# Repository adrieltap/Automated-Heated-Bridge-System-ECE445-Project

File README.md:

# ACADEMIC INTEGRITY
Please review the University of Illinois Student Code before starting, particularly all subsections of Article 1, Part 4 Academic Integrity and Procedure here.

§ 1‑402 Academic Integrity Infractions

(a). Cheating. No student shall use or attempt to use in any academic exercise materials, information, study aids, or electronic data that the student knows or should know is unauthorized. Instructors are strongly encouraged to make in advance a clear statement of their policies and procedures concerning the use of shared study aids, examination files, and related materials and forms of assistance. Such advance notification is especially important in the case of take-home examinations. During any examination, students should assume that external assistance (e.g., books, notes, calculators, and communications with others) is prohibited unless specifically authorized by the Instructor. A violation of this section includes but is not limited to:

(1) Allowing others to conduct research or prepare any work for a student without prior authorization from the Instructor, including using the services of commercial term paper companies.

(2) Submitting substantial portions of the same academic work for credit more than once or by more than one student without authorization from the Instructors to whom the work is being submitted.

(3) Working with another person without authorization to satisfy an individual assignment.

(b) Plagiarism. No student shall represent the words, work, or ideas of another as his or her own in any academic endeavor. A violation of this section includes but is not limited to:

(1) Copying: Submitting the work of another as one’s own.

(2) Direct Quotation: Every direct quotation must be identified by quotation marks or by appropriate indentation and must be promptly cited. Proper citation style for many academic departments is outlined in such manuals as the MLA Handbook or K.L. Turabian’s A Manual for Writers of Term Papers, Theses and Dissertations. These and similar publications are available in the University bookstore or library. The actual source from which cited information was obtained should be acknowledged.

(3) Paraphrase: Prompt acknowledgment is required when material from another source is paraphrased or summarized in whole or in part. This is true even if the student’s words differ substantially from those of the source. A citation acknowledging only a directly quoted statement does not suffice as an acknowledgment of any preceding or succeeding paraphrased material.

(4) Borrowed Facts or Information: Information obtained in one’s reading or research that is not common knowledge must be acknowledged. Examples of common knowledge might include the names of leaders of prominent nations, basic scientific laws, etc. Materials that contribute only to one’s general understanding of the subject may be acknowledged in a bibliography and need not be immediately cited. One citation is usually sufficient to acknowledge indebtedness when a number of connected sentences in the paper draw their special information from one source.

(c) Fabrication. No student shall falsify or invent any information or citation in an academic endeavor. A violation of this section includes but is not limited to:

(1) Using invented information in any laboratory experiment or other academic endeavor without notice to and authorization from the Instructor or examiner. It would be improper, for example, to analyze one sample in an experiment and covertly invent data based on that single experiment for several more required analyses.

(2) Altering the answers given for an exam after the examination has been graded.

(3) Providing false or misleading information for the purpose of gaining an academic advantage.

(d) Facilitating Infractions of Academic Integrity. No student shall help or attempt to help another to commit an infraction of academic integrity, where one knows or should know that through one’s acts or omissions such an infraction may be facilitated. A violation of this section includes but is not limited to:

(1) Allowing another to copy from one’s work.

(2) Taking an exam by proxy for someone else. This is an infraction of academic integrity on the part of both the student enrolled in the course and the proxy or substitute.

(3) Removing an examination or quiz from a classroom, faculty office, or other facility without authorization.

(e) Bribes, Favors, and Threats. No student shall bribe or attempt to bribe, promise favors to or make threats against any person with the intent to affect a record of a grade or evaluation of academic performance. This includes conspiracy with another person who then takes the action on behalf of the student.

(f) Academic Interference. No student shall tamper with, alter, circumvent, or destroy any educational material or resource in a manner that deprives any other student of fair access or reasonable use of that material or resource.

(1) Educational resources include but are not limited to computer facilities, electronic data, required/reserved readings, reference works, or other library materials.

(2) Academic interference also includes acts in which the student committing the infraction personally benefits from the interference, regardless of the effect on other students.

LEGAL
Permission to use, copy, modify, and distribute this software and its documentation for any purpose, without fee, and without written agreement is hereby granted, provided that the above copyright notice and the following two paragraphs appear in all copies of this software.

IN NO EVENT SHALL THE AUTHOR OR THE UNIVERSITY OF ILLINOIS BE LIABLE TO ANY PARTY FOR DIRECT, INDIRECT, SPECIAL, INCIDENTAL, OR CONSEQUENTIAL DAMAGES ARISING OUT OF THE USE OF THIS SOFTWARE AND ITS DOCUMENTATION, EVEN IF THE AUTHOR AND/OR THE UNIVERSITY OF ILLINOIS HAS BEEN ADVISED OF THE POSSIBILITY OF SUCH DAMAGE.

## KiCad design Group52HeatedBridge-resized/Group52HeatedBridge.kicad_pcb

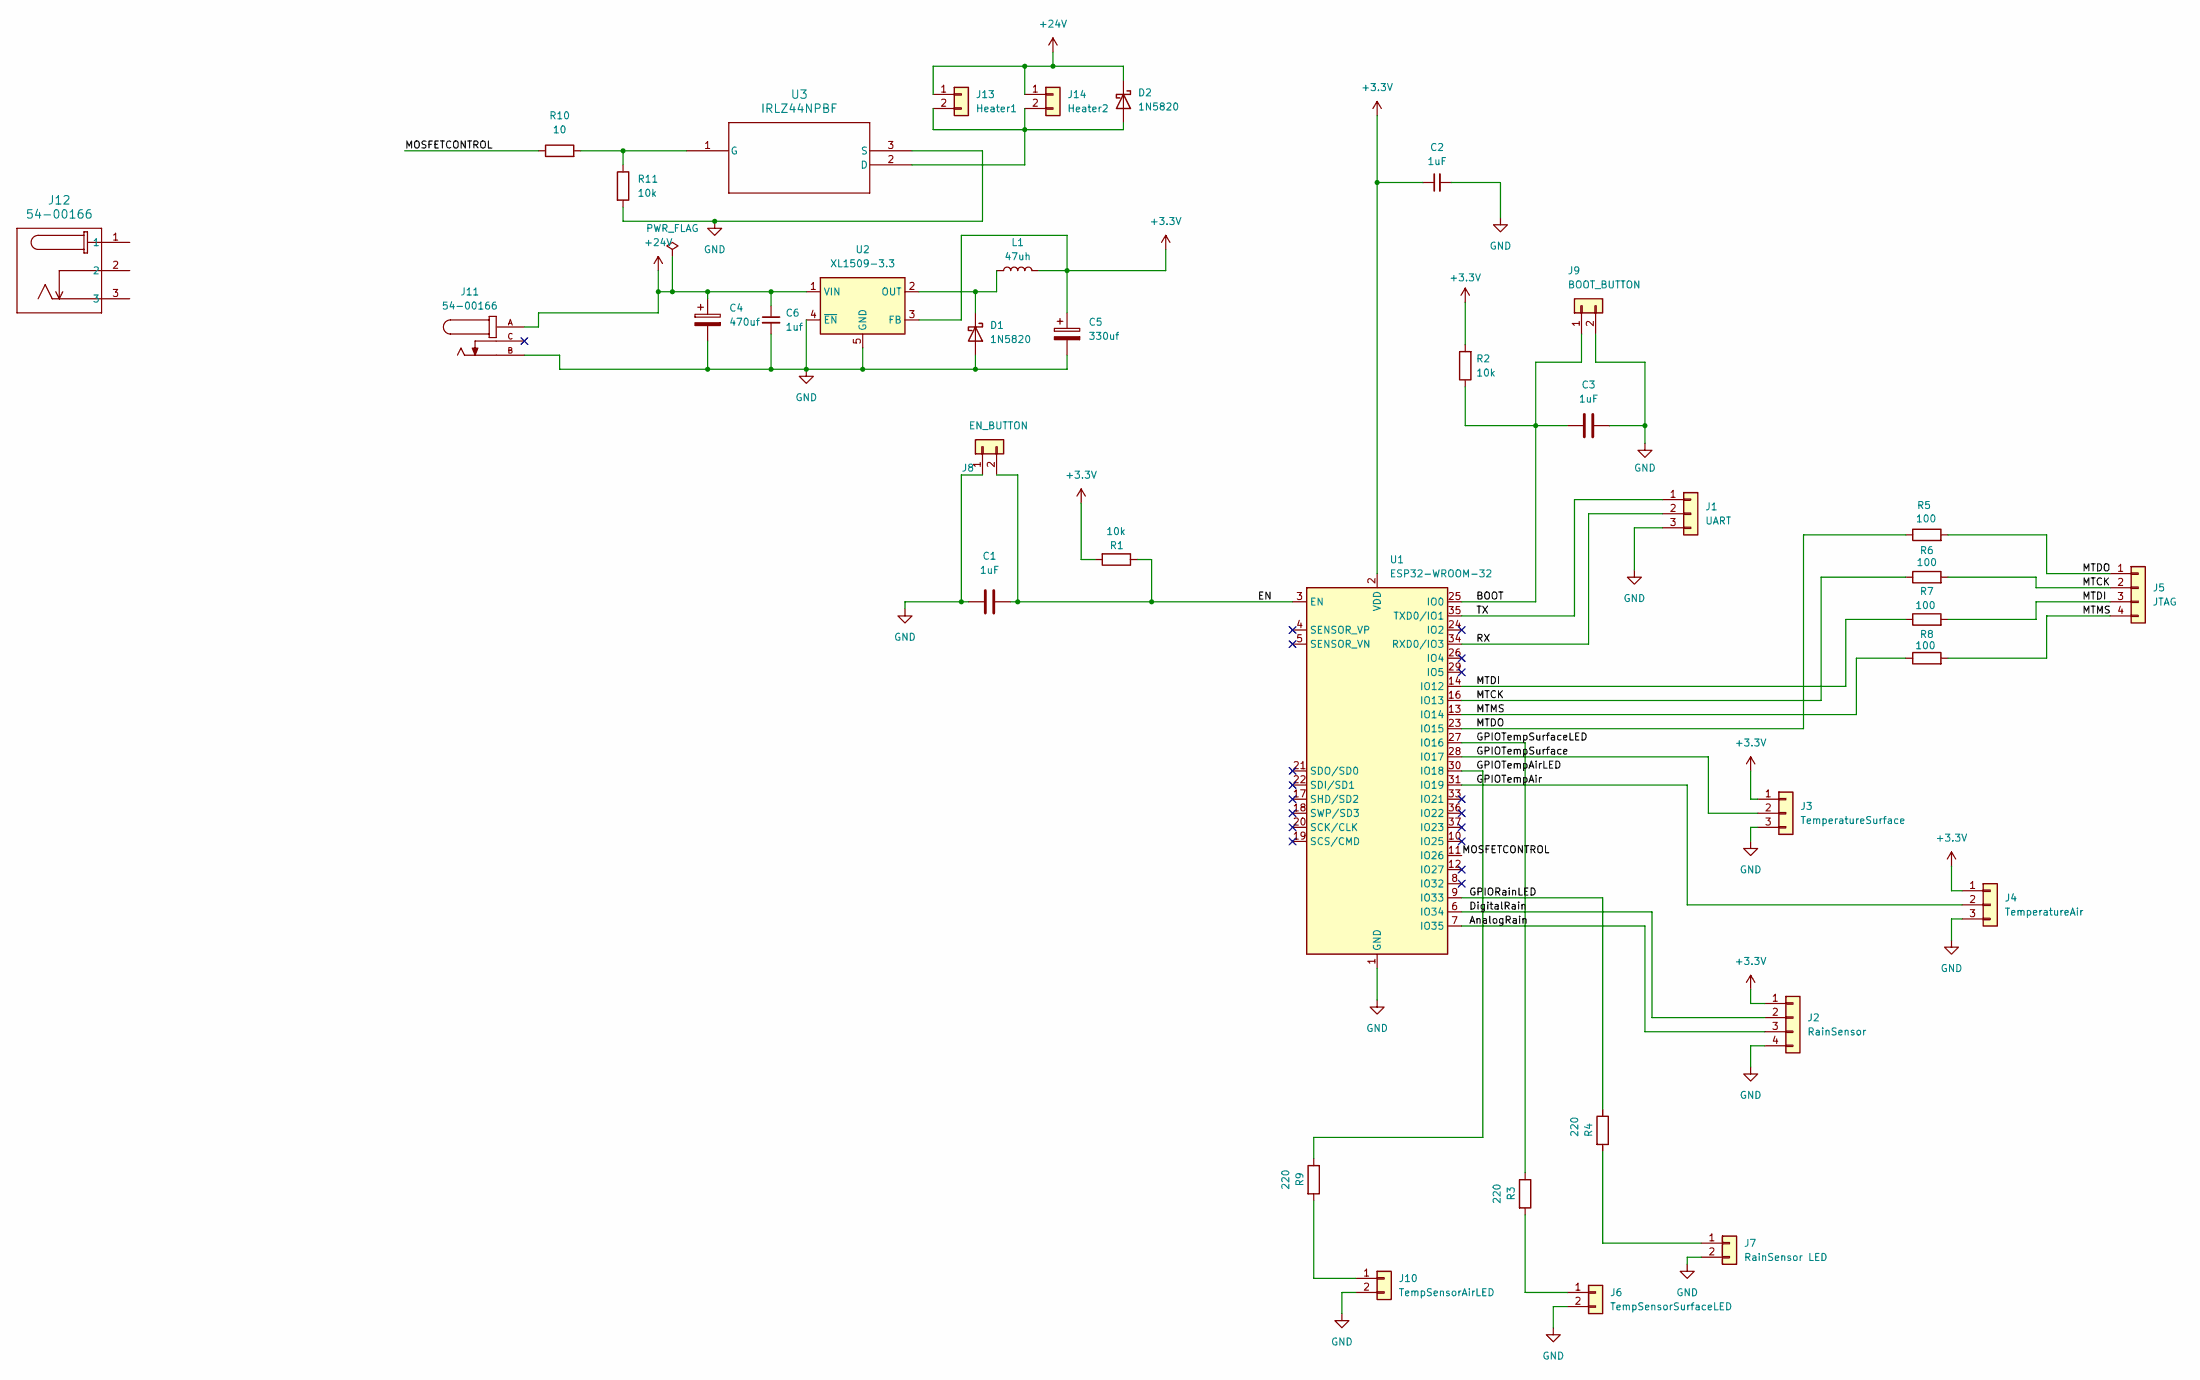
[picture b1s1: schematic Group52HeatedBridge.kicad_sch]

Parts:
C1, C2, C3: 1uF; C_0805_2012Metric_Pad1.18x1.45mm_HandSolder
C4: 470uf; C_0805_2012Metric_Pad1.18x1.45mm_HandSolder
C5: 330uf; C_0805_2012Metric_Pad1.18x1.45mm_HandSolder
C6: 1uf; C_0805_2012Metric_Pad1.18x1.45mm_HandSolder
D1, D2: 1N5820; D_DO-201AD_P3.81mm_Vertical_KathodeUp
J1: UART; Molex_KK-254_AE-6410-03A_1x03_P2.54mm_Vertical
J2: RainSensor; Molex_KK-254_AE-6410-04A_1x04_P2.54mm_Vertical
J3: TemperatureSurface; Molex_KK-254_AE-6410-03A_1x03_P2.54mm_Vertical
J4: TemperatureAir; Molex_KK-254_AE-6410-03A_1x03_P2.54mm_Vertical
J5: JTAG; Molex_KK-254_AE-6410-04A_1x04_P2.54mm_Vertical
J6: TempSensorSurfaceLED; Molex_KK-254_AE-6410-02A_1x02_P2.54mm_Vertical
J7: RainSensor LED; Molex_KK-254_AE-6410-02A_1x02_P2.54mm_Vertical
J8: EN_BUTTON; Molex_KK-254_AE-6410-02A_1x02_P2.54mm_Vertical
J9: BOOT_BUTTON; Molex_KK-254_AE-6410-02A_1x02_P2.54mm_Vertical
J10: TempSensorAirLED; Molex_KK-254_AE-6410-02A_1x02_P2.54mm_Vertical
J11: 54-00166; TENSILITY_54-00166; PARTREV A
J12: 54-00166; TENSILITY_54-00166
J13: Heater1; Molex_KK-254_AE-6410-02A_1x02_P2.54mm_Vertical
J14: Heater2; Molex_KK-254_AE-6410-02A_1x02_P2.54mm_Vertical
L1: 47uh; L_0805_2012Metric_Pad1.15x1.40mm_HandSolder
R1, R2, R11: 10k; R_0805_2012Metric_Pad1.20x1.40mm_HandSolder
R3, R4, R9: 220; R_0805_2012Metric_Pad1.20x1.40mm_HandSolder
R5, R6, R7, R8: 100; R_0805_2012Metric_Pad1.20x1.40mm_HandSolder
R10: 10; R_0805_2012Metric_Pad1.20x1.40mm_HandSolder
U1: ESP32-WROOM-32
U2: XL1509-3.3; SOIC-8_3.9x4.9mm_P1.27mm
U3: IRLZ44NPBF; PG-TO220-3_INF

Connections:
+3.3V: C2.1, C5.1, J2.1, J3.1, J4.1, L1.2, R1.2, R2.2, U1.2 (VDD), U2.3 (FB)
+24V: C4.1, C6.1, D2.1 (K), J11.A, J13.1, J14.1, U2.1 (VIN)
/AnalogRain: J2.3, U1.7 (IO35)
/BOOT: C3.1, J9.1, R2.1, U1.25 (IO0)
/DigitalRain: J2.2, U1.6 (IO34)
/EN: C1.2, J8.2, R1.1, U1.3 (EN)
/GPIORainLED: R4.1, U1.9 (IO33)
/GPIOTempAir: J4.2, U1.31 (IO19)
/GPIOTempAirLED: R9.1, U1.30 (IO18)
/GPIOTempSurface: J3.2, U1.28 (IO17)
/GPIOTempSurfaceLED: R3.1, U1.27 (IO16)
/MOSFETCONTROL: R10.1, U1.11 (IO26)
/MTCK: J5.2, R6.1, R6.2, U1.16 (IO13)
/MTDI: J5.3, R7.1, R7.2, U1.14 (IO12)
/MTDO: J5.1, R5.1, R5.2, U1.23 (IO15)
/MTMS: J5.4, R8.1, R8.2, U1.13 (IO14)
/RX: J1.2, U1.34 (RXD0/IO3)
/TX: J1.1, U1.35 (TXD0/IO1)
GND: C1.1, C2.2, C3.2, C4.2, C5.2, C6.2, D1.2 (A), J1.3, J2.4, J3.3, J4.3, J6.2, J7.2, J8.1, J9.2, J10.2, J11.B, R11.2, U1.1 (GND), U1.15 (GND), U1.38 (GND), U1.39 (GND), U2.4 (~EN), U2.5 (GND), U2.6 (GND), U2.7 (GND), U2.8 (GND), U3.3 (S)
unnamed: D1.1 (K), L1.1, U2.2 (OUT)
unnamed: D2.2 (A), J13.2, J14.2, U3.2 (D)
unnamed: J6.1, R3.2
unnamed: J7.1, R4.2
unnamed: J10.1, R9.2
unnamed: R10.2, R11.1, U3.1 (G)

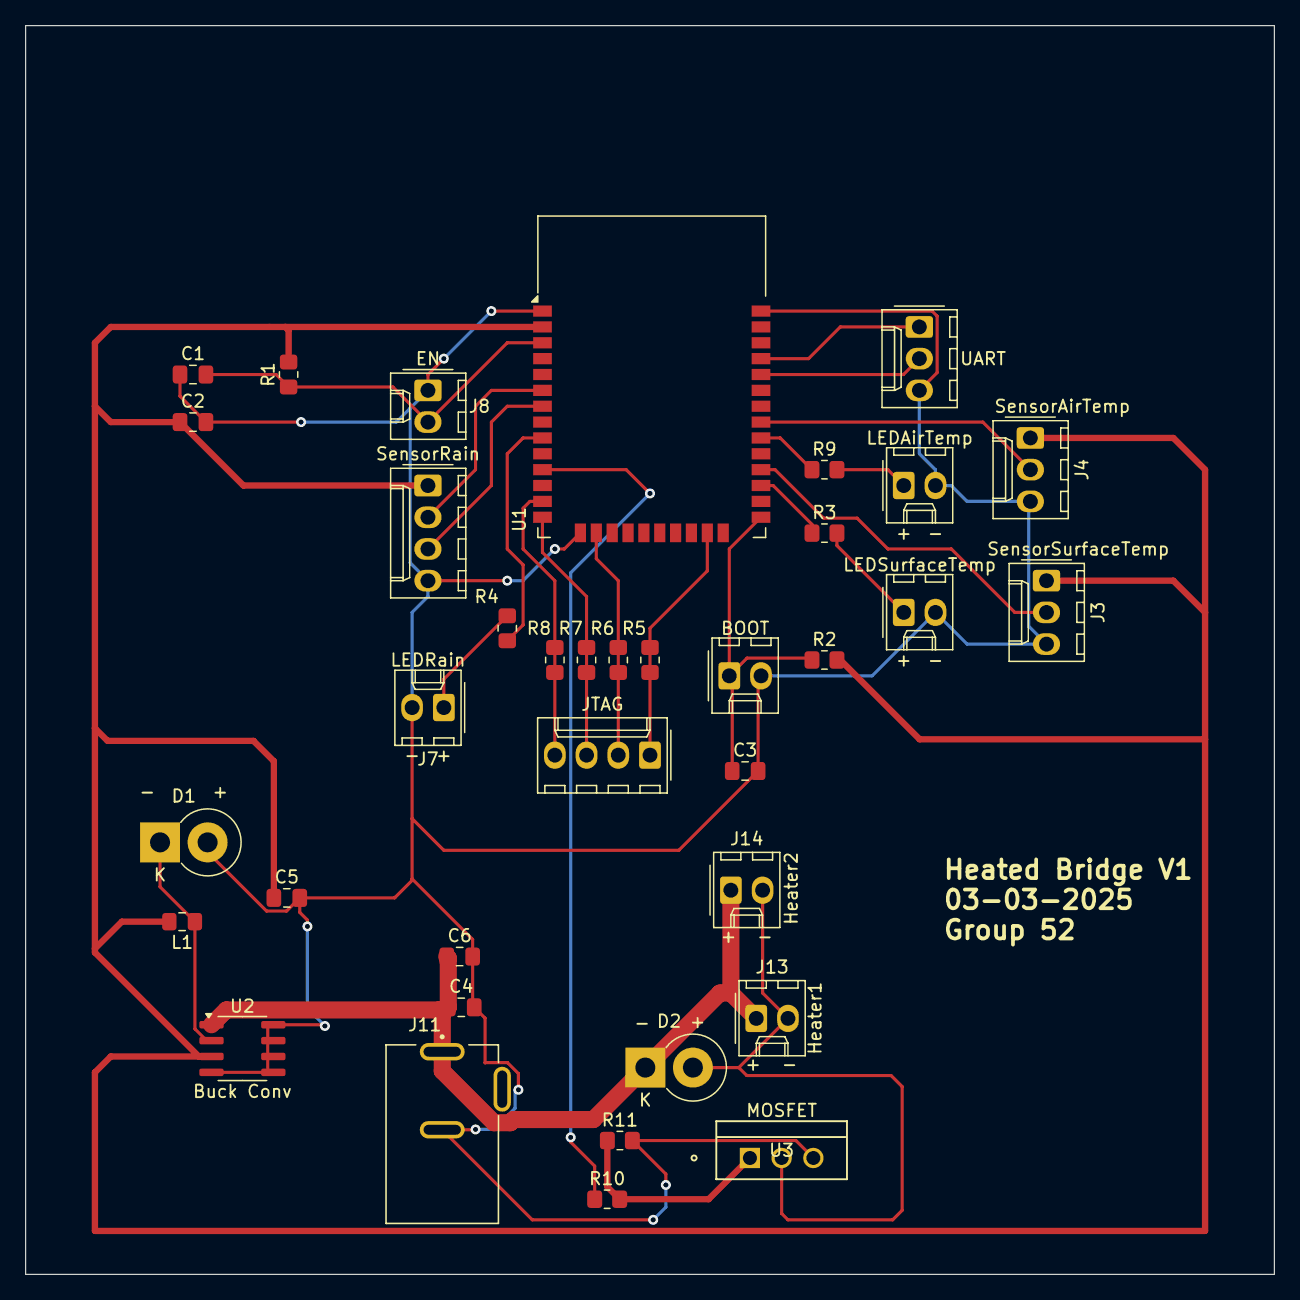
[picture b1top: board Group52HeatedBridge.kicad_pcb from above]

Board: 2 copper layers, 100.0 x 100.0 mm, 36 parts (0 on the bottom side), 25 nets.

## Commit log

2025-02-17 added gitignore file
2025-02-17 added git ignroe
2025-02-19 added more entries
2025-02-24 switching to a digital notebook :"
2025-02-24 parts for power supply
2025-02-24 notes update
2025-02-24 updated notebook
2025-02-24 notes updated
2025-02-26 added schematic
2025-02-26 added deleted schematic
2025-02-26 added connectors and researched new temp sensor that is waterproof and easy to interface with
2025-02-28 updated schematic
2025-02-28 grid size update fix
2025-02-28 Added IO and rain sensor to schematic
2025-02-28 scematic passes DRC except one error where we need to draw the actual physical border of our PCB, components are flipped tho
2025-02-28 added footprints for barell jack
2025-02-28 added more labels for orientation
2025-03-02 power subsytem schematic
2025-03-02 power subsytem schematic - more chnages
2025-03-02 power subsytem schematic push - second try
2025-03-03 power subsytem schematic push - second
2025-03-03 resized schematic and cleaned up
2025-03-03 B Revert "resized schematic and cleaned up"
    This reverts commit bab35e5b8986f5439bb45f55d315508e4487ff8d.
    reverted auto save file
2025-03-03 resize schematic
2025-03-03 resized schematic
2025-03-03 pushing the resized version from adriel
2025-03-03 passes pcbway audit
2025-03-08 cleaned branch
2025-03-09 added code for breadboard demo, got the breadboard working as well
2025-03-12 no chnages just cleanup
2025-03-13 cleaned up repo, only push after the zip file when archiving the project
2025-03-20 added ground plane + first pass of having the right trace widths
2025-03-24 cleaned up pcb, added new esp32, added jumper wire between the 2 subsystems
2025-03-24 added testpoints
2025-03-27 added test points, mosfet footprint etc
2025-03-27 added extra decoupling capacitor
2025-03-27 ordered second round
2025-04-06 changed capacitors
2025-04-07 Added BLE server and receiver code
2025-04-13 updated pull up resistors
2025-04-15 test
2025-04-15 removed test file
2025-04-15 added lib folder
2025-04-15 updated laptop code
2025-04-15 added lib to branch
2025-04-16 updated control system
2025-04-16 fixed pin numbers in control_system
2025-04-16 changed pins
2025-04-23 added thresholds and fixed logic of code
2025-04-24 updated code
2025-04-24 Pre duplex
2025-04-26 added functionality to change thresholds through bluetooth and fixed event loop
2025-04-27 updated UI stuff
2025-04-27 added csv functionality
2025-04-27 reset btn
2025-04-28 added comments
2025-05-08 added updated lab notebooks
2025-05-08 updated lab notebook
2025-05-08 added labnotebook
2025-05-08 update labnotebooks
2025-05-08 moved images to my notebook dir
2025-05-08 moved image files
2025-05-09 added update to notebook
2025-05-09 another lab notebook update
2025-05-09 final update
